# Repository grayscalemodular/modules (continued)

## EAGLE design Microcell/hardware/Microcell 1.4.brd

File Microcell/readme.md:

Microcell
=======

[microcell](https://microcell.cc) is a Eurorack synthesizer module created by [Grayscale](https://grayscale.info/). It is primarily based on [Clouds](https://mutable-instruments.net/modules/clouds/) by [Mutable Instruments](https://mutable-instruments.net/), which was discontinued in 2017. The original source files for Clouds can be found in the Mutable Instruments [Github](https://github.com/pichenettes/eurorack) repository.

Visit [microcell.cc](https://microcell.cc) for more information.

Hardware
=======

The schematic and PCB files for this project are distributed under the Creative Commons [CC-BY-SA 3.0](https://creativecommons.org/licenses/by-sa/3.0/) license, the same license used by the Clouds source files.

CC BY-SA license terms do not confer the right to use intellectual property such as trademarks, brand names, and logos. Grayscale, Microcell, Mutable Instruments, and Clouds are trademarks of their respective owners and should not be used without permission.

Firmware
=======

Microcell ships with the Superparasites firmware, which combines elements of the original Clouds DSP code by [Mutable Instruments](https://github.com/pichenettes/eurorack), the [Parasites](https://mqtthiqs.github.io/parasites/clouds.html) alternate firmware by Matthias Puech, and the [Beat Repeat](https://github.com/jkammerl/eurorack) alternate firmware by Julius Kammerl. All source code is available on the [GitHub repo](https://github.com/patrickdowling/superparasites) maintained by Patrick Dowling. Thanks to all involved for their work on this hybrid code base.

Source code for this project is distributed under the MIT License. See [github.com/patrickdowling/superparasites](https://github.com/patrickdowling/superparasites) for source code.

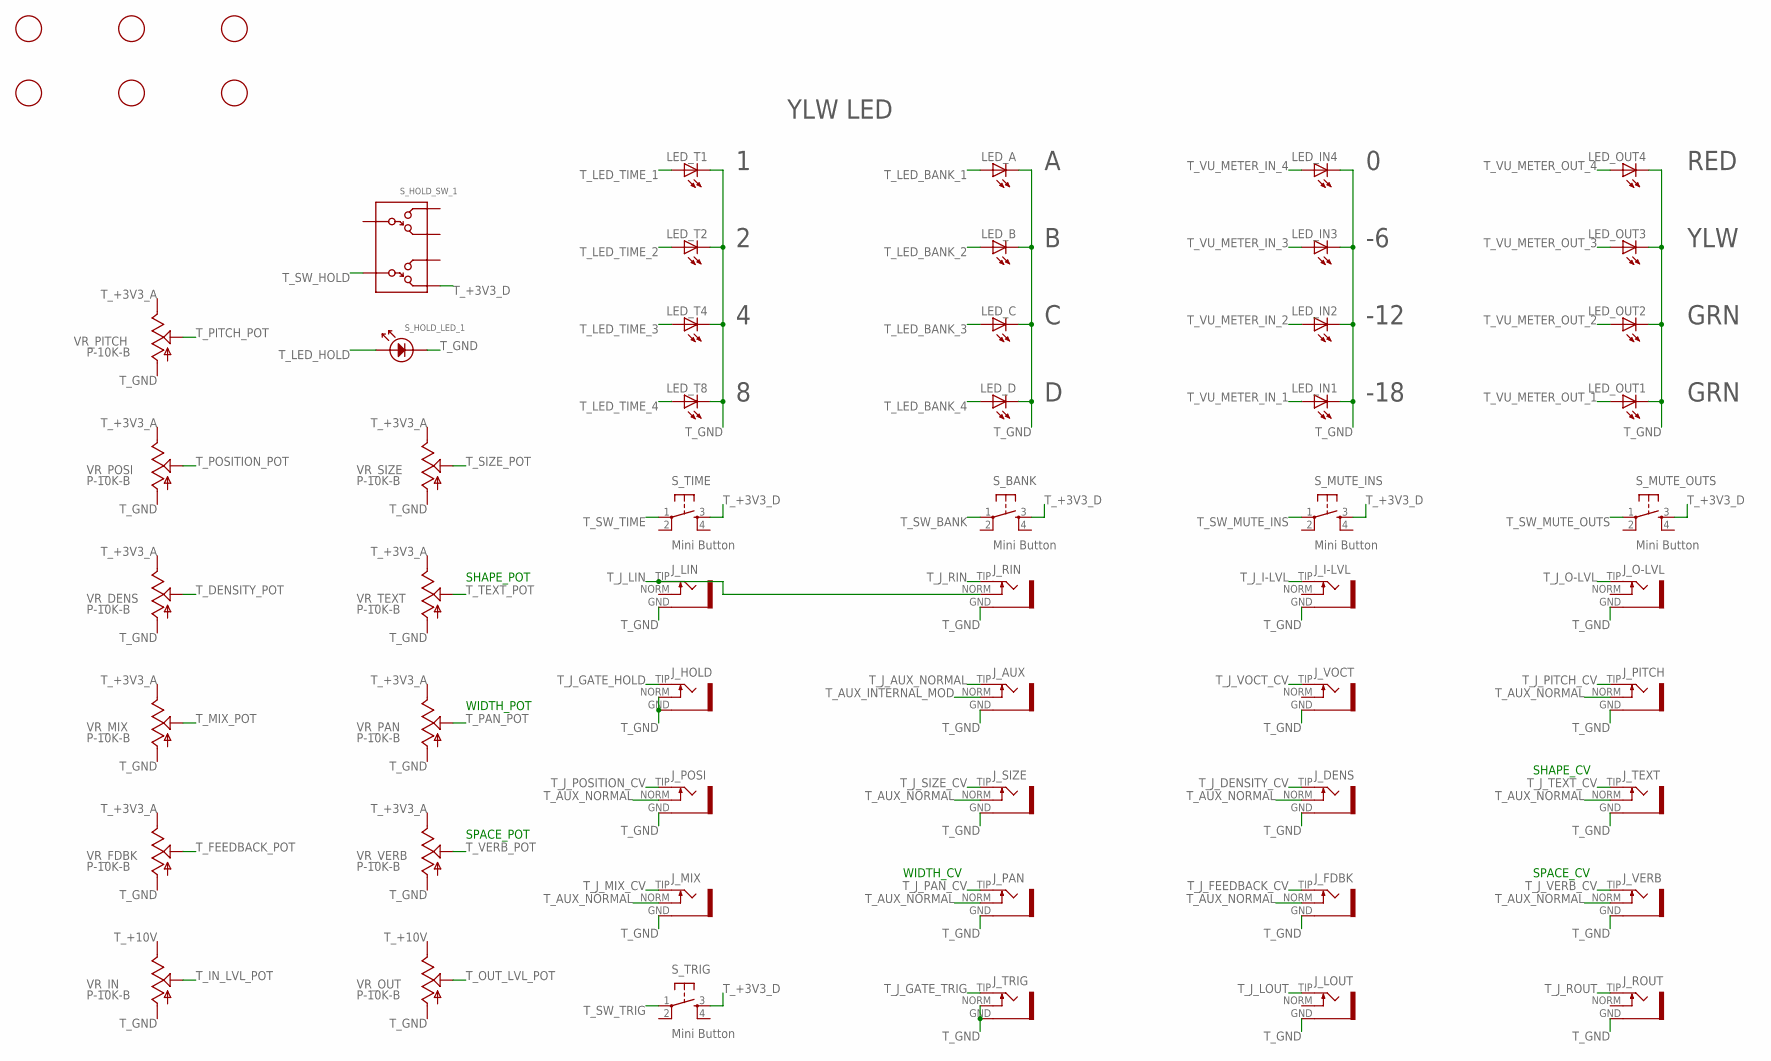
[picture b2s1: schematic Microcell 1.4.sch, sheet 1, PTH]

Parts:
FD1, FD2, FD3, FD4, FD5, FD6: FIDUCIAL; FIDUCIAL_1MM
J_AUX: Eurorack Jack; S_JACK_SMALL_SILK
J_DENS: Eurorack Jack; S_JACK_SILK
J_FDBK: Eurorack Jack; S_JACK_SILK
J_HOLD: Eurorack Jack; S_JACK_SMALL_SILK
J_I-LVL: Eurorack Jack; S_JACK_SILK
J_LIN: Eurorack Jack; S_JACK_SILK
J_LOUT: Eurorack Jack; S_JACK_SILK
J_MIX: Eurorack Jack; S_JACK_SILK
J_O-LVL: Eurorack Jack; S_JACK_SILK
J_PAN: Eurorack Jack; S_JACK_SILK
J_PITCH: Eurorack Jack; S_JACK_SILK
J_POSI: Eurorack Jack; S_JACK_SILK
J_RIN: Eurorack Jack; S_JACK_SILK
J_ROUT: Eurorack Jack; S_JACK_SILK
J_SIZE: Eurorack Jack; S_JACK_SILK
J_TEXT: Eurorack Jack; S_JACK_SILK
J_TRIG: Eurorack Jack; S_JACK_SMALL_SILK
J_VERB: Eurorack Jack; S_JACK_SILK
J_VOCT: Eurorack Jack; S_JACK_SILK
LED_A: 3mm Yellow Diffused; LED_SILK
LED_B: 3mm Yellow Diffused; LED_SILK
LED_C: 3mm Yellow Diffused; LED_SILK
LED_D: 3mm Yellow Diffused; LED_SILK
LED_IN1, LED_IN2: 3mm Green Diffused; LED_SILK
LED_IN3: 3mm Yellow Diffused; LED_SILK
LED_IN4: 3mm Red Diffused; LED_SILK
LED_OUT1, LED_OUT2: 3mm Green Diffused; LED_SILK
LED_OUT3: 3mm Yellow Diffused; LED_SILK
LED_OUT4: 3mm Red Diffused; LED_SILK
LED_T1, LED_T2, LED_T4, LED_T8: 3mm Yellow Diffused; LED_SILK
S_BANK: Mini Button; TACTILE-PTH_SILK
S_HOLD: LED Button White; LED_BUTTON_SILK
S_MUTE_INS: Mini Button; TACTILE-PTH_SILK
S_MUTE_OUTS: Mini Button; TACTILE-PTH_SILK
S_TIME: Mini Button; TACTILE-PTH_SILK
S_TRIG: Mini Button; TACTILE-PTH_SILK
VR_DENS: P-10K-B; 9MM_SNAP-IN_POT_SILK
VR_FDBK: P-10K-B; 9MM_SNAP-IN_POT_SILK
VR_IN: P-10K-B; 9MM_SNAP-IN_POT_SILK
VR_MIX: P-10K-B; 9MM_SNAP-IN_POT_SILK
VR_OUT: P-10K-B; 9MM_SNAP-IN_POT_SILK
VR_PAN: P-10K-B; 9MM_SNAP-IN_POT_SILK
VR_PITCH: P-10K-B; 9MM_SNAP-IN_POT_SILK
VR_POSI: P-10K-B; 9MM_SNAP-IN_POT_SILK
VR_SIZE: P-10K-B; 9MM_SNAP-IN_POT_SILK
VR_TEXT: P-10K-B; 9MM_SNAP-IN_POT_SILK
VR_VERB: P-10K-B; 9MM_SNAP-IN_POT_SILK

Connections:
T_+3V3_A: VR_DENS.3, VR_FDBK.3, VR_MIX.3, VR_PAN.3, VR_PITCH.3, VR_POSI.3, VR_SIZE.3, VR_TEXT.3, VR_VERB.3; also elsewhere on the board
T_+3V3_D: S_BANK.3, S_HOLD.3, S_MUTE_INS.3, S_MUTE_OUTS.3, S_TIME.3, S_TRIG.3; also elsewhere on the board
T_+10V: VR_IN.3, VR_OUT.3; also elsewhere on the board
T_AUX_INTERNAL_MOD: J_AUX.NORM; also elsewhere on the board
T_AUX_NORMAL: J_DENS.NORM, J_FDBK.NORM, J_MIX.NORM, J_PAN.NORM, J_PITCH.NORM, J_POSI.NORM, J_SIZE.NORM, J_TEXT.NORM, J_VERB.NORM; also elsewhere on the board
T_DENSITY_POT: VR_DENS.2; also elsewhere on the board
T_FEEDBACK_POT: VR_FDBK.2; also elsewhere on the board
T_GND: J_AUX.GND, J_DENS.GND, J_FDBK.GND, J_HOLD.GND, J_HOLD.NORM, J_I-LVL.GND, J_LIN.GND, J_LOUT.GND, J_MIX.GND, J_O-LVL.GND, J_PAN.GND, J_PITCH.GND, J_POSI.GND, J_RIN.GND, J_ROUT.GND, J_SIZE.GND, J_TEXT.GND, J_TRIG.GND, J_TRIG.NORM, J_VERB.GND, J_VOCT.GND, LED_A.K (C), LED_B.K (C), LED_C.K (C), LED_D.K (C), LED_IN1.K (C), LED_IN2.K (C), LED_IN3.K (C), LED_IN4.K (C), LED_OUT1.K (C), LED_OUT2.K (C), LED_OUT3.K (C), LED_OUT4.K (C), LED_T1.K (C), LED_T2.K (C), LED_T4.K (C), LED_T8.K (C), S_HOLD.LED_K, VR_DENS.1, VR_FDBK.1, VR_IN.1, VR_MIX.1, VR_OUT.1, VR_PAN.1, VR_PITCH.1, VR_POSI.1, VR_SIZE.1, VR_TEXT.1, VR_VERB.1; also elsewhere on the board
T_IN_LVL_POT: VR_IN.2; also elsewhere on the board
T_J_AUX_NORMAL: J_AUX.TIP; also elsewhere on the board
T_J_DENSITY_CV: J_DENS.TIP; also elsewhere on the board
T_J_FEEDBACK_CV: J_FDBK.TIP; also elsewhere on the board
T_J_GATE_HOLD: J_HOLD.TIP; also elsewhere on the board
T_J_GATE_TRIG: J_TRIG.TIP; also elsewhere on the board
T_J_I-LVL: J_I-LVL.TIP; also elsewhere on the board
T_J_LIN: J_LIN.TIP, J_RIN.NORM; also elsewhere on the board
T_J_LOUT: J_LOUT.TIP; also elsewhere on the board
T_J_MIX_CV: J_MIX.TIP; also elsewhere on the board
T_J_O-LVL: J_O-LVL.TIP; also elsewhere on the board
T_J_PAN_CV: J_PAN.TIP; also elsewhere on the board
T_J_PITCH_CV: J_PITCH.TIP; also elsewhere on the board
T_J_POSITION_CV: J_POSI.TIP; also elsewhere on the board
T_J_RIN: J_RIN.TIP; also elsewhere on the board
T_J_ROUT: J_ROUT.TIP; also elsewhere on the board
T_J_SIZE_CV: J_SIZE.TIP; also elsewhere on the board
T_J_TEXT_CV: J_TEXT.TIP; also elsewhere on the board
T_J_VERB_CV: J_VERB.TIP; also elsewhere on the board
T_J_VOCT_CV: J_VOCT.TIP; also elsewhere on the board
T_LED_BANK_1: LED_A.A; also elsewhere on the board
T_LED_BANK_2: LED_B.A; also elsewhere on the board
T_LED_BANK_3: LED_C.A; also elsewhere on the board
T_LED_BANK_4: LED_D.A; also elsewhere on the board
T_LED_HOLD: S_HOLD.LED_A; also elsewhere on the board
T_LED_TIME_1: LED_T1.A; also elsewhere on the board
T_LED_TIME_2: LED_T2.A; also elsewhere on the board
T_LED_TIME_3: LED_T4.A; also elsewhere on the board
T_LED_TIME_4: LED_T8.A; also elsewhere on the board
T_MIX_POT: VR_MIX.2; also elsewhere on the board
T_OUT_LVL_POT: VR_OUT.2; also elsewhere on the board
T_PAN_POT: VR_PAN.2; also elsewhere on the board
T_PITCH_POT: VR_PITCH.2; also elsewhere on the board
T_POSITION_POT: VR_POSI.2; also elsewhere on the board
T_SIZE_POT: VR_SIZE.2; also elsewhere on the board
T_SW_BANK: S_BANK.1; also elsewhere on the board
T_SW_HOLD: S_HOLD.2; also elsewhere on the board
T_SW_MUTE_INS: S_MUTE_INS.1; also elsewhere on the board
T_SW_MUTE_OUTS: S_MUTE_OUTS.1; also elsewhere on the board
T_SW_TIME: S_TIME.1; also elsewhere on the board
T_SW_TRIG: S_TRIG.1; also elsewhere on the board
T_TEXT_POT: VR_TEXT.2; also elsewhere on the board
T_VERB_POT: VR_VERB.2; also elsewhere on the board
T_VU_METER_IN_1: LED_IN1.A; also elsewhere on the board
T_VU_METER_IN_2: LED_IN2.A; also elsewhere on the board
T_VU_METER_IN_3: LED_IN3.A; also elsewhere on the board
T_VU_METER_IN_4: LED_IN4.A; also elsewhere on the board
T_VU_METER_OUT_1: LED_OUT1.A; also elsewhere on the board
T_VU_METER_OUT_2: LED_OUT2.A; also elsewhere on the board
T_VU_METER_OUT_3: LED_OUT3.A; also elsewhere on the board
T_VU_METER_OUT_4: LED_OUT4.A; also elsewhere on the board

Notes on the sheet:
-12
-18
GRN
YLW
RED
YLW LED
SPACE_CV
SHAPE_CV
WIDTH_CV
WIDTH_POT
SHAPE_POT
SPACE_POT

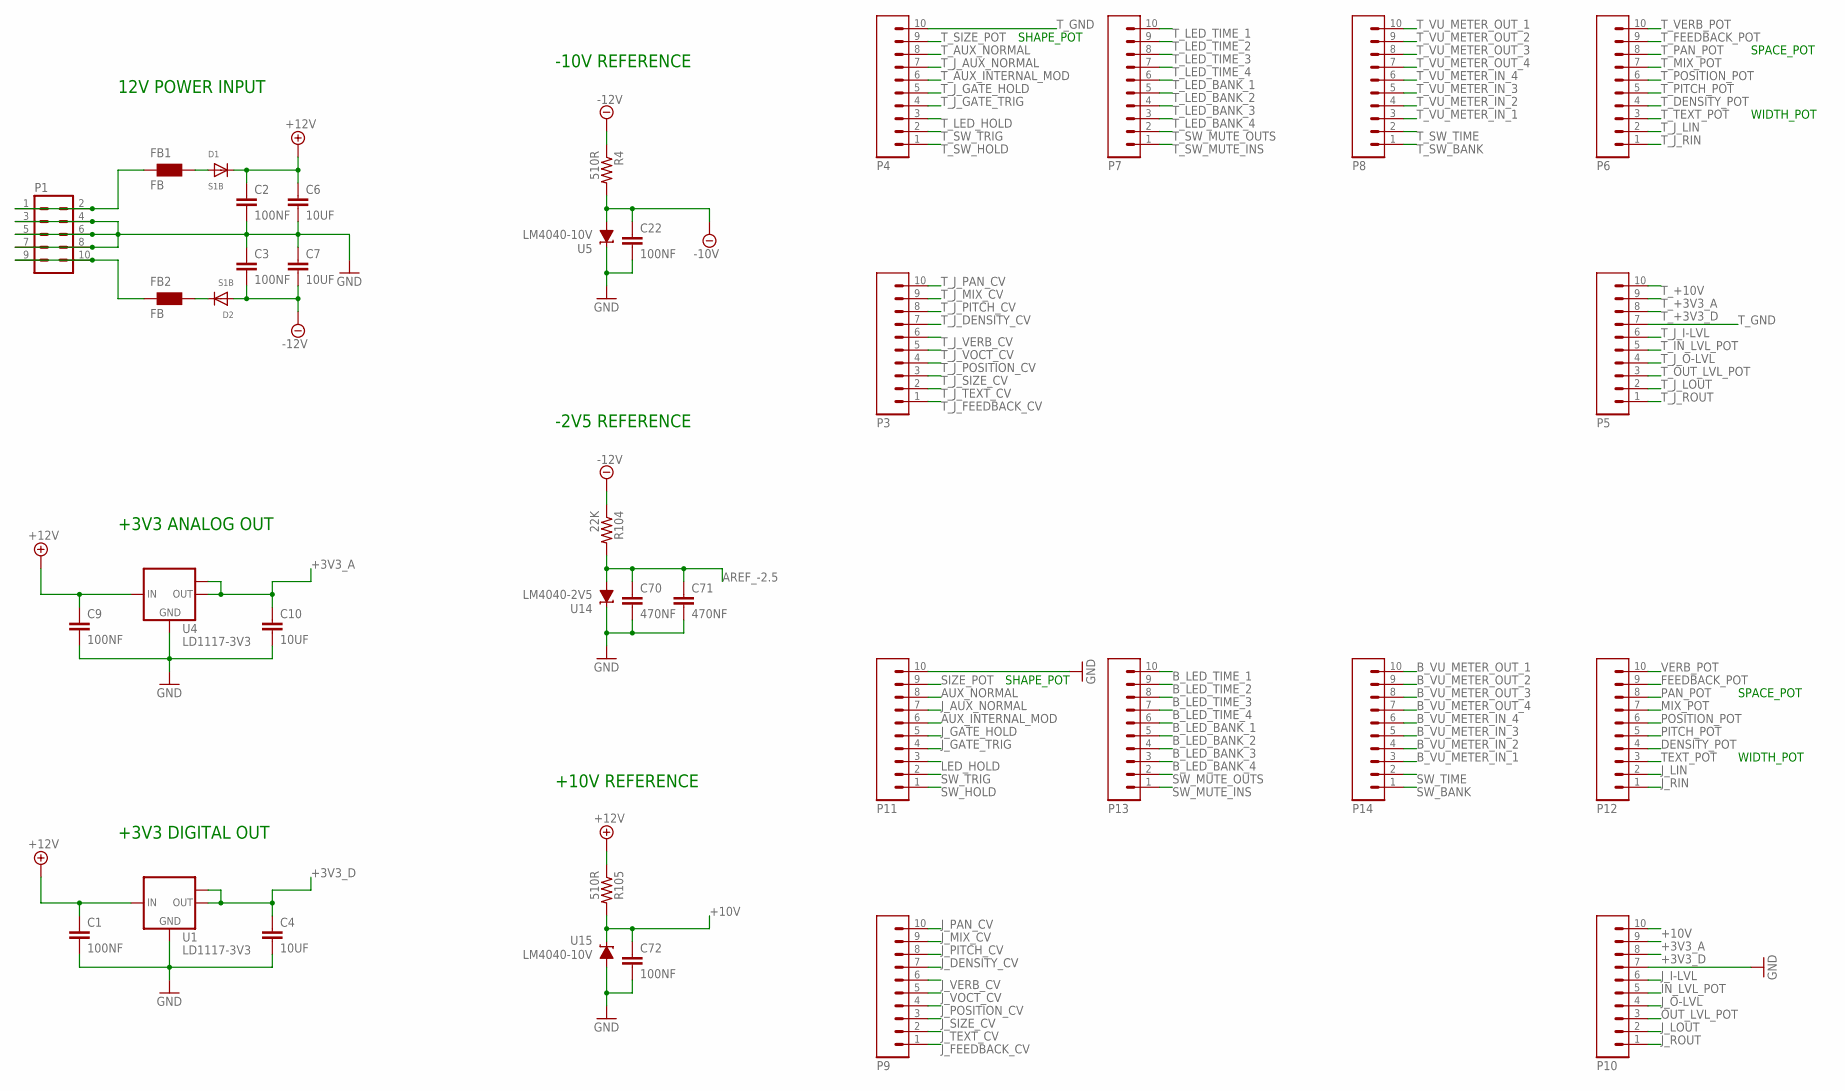
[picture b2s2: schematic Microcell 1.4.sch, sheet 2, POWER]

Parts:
C1, C2, C3, C9, C22, C72: 100NF; C0603
C4, C6, C7, C10: 10UF; C0805
C70, C71: 470NF; C0603
D1, D2: S1B; SMADIODE
FB1, FB2: FB; WUERTH-ELEKTRONIK_0603
P1: 2X5 Male PTH Header; 2X5_LOCK
P3, P4, P5, P6, P7, P8: 1X10 Female PTH header; 1X10_NO_SILK
P9, P10, P11, P12, P13, P14: 1X10 Male PTH header; 1X10_NO_SILK
R4, R105: 510R; R0603
R104: 22K; R0603
U1, U4: LD1117-3V3; SOT223
U5, U15: LM4040-10V; DBZ_R-PDSO-G3
U14: LM4040-2V5; DBZ_R-PDSO-G3

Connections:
+3V3_A: C10.1, P10.9, U4.2 (OUT), U4.TAB (OUT1); also elsewhere on the board
+3V3_D: C4.1, P10.8, U1.2 (OUT), U1.TAB (OUT1); also elsewhere on the board
+10V: C72.1, P10.10, R105.2, U15.1 (C)
+12V: C1.1, C2.1, C6.1, C9.1, D1.C, R105.1, U1.3 (IN), U4.3 (IN); also elsewhere on the board
-10V: C22.1, R4.2, U5.2 (A); also elsewhere on the board
-12V: C3.2, C7.2, D2.A, R4.1, R104.1; also elsewhere on the board
AREF_-2.5: C70.1, C71.1, R104.2, U14.2 (A); also elsewhere on the board
AUX_INTERNAL_MOD: P11.6; also elsewhere on the board
AUX_NORMAL: P11.8; also elsewhere on the board
B_LED_BANK_1: P13.6; also elsewhere on the board
B_LED_BANK_2: P13.5; also elsewhere on the board
B_LED_BANK_3: P13.4; also elsewhere on the board
B_LED_BANK_4: P13.3; also elsewhere on the board
B_LED_TIME_1: P13.10; also elsewhere on the board
B_LED_TIME_2: P13.9; also elsewhere on the board
B_LED_TIME_3: P13.8; also elsewhere on the board
B_LED_TIME_4: P13.7; also elsewhere on the board
B_VU_METER_IN_1: P14.3; also elsewhere on the board
B_VU_METER_IN_2: P14.4; also elsewhere on the board
B_VU_METER_IN_3: P14.5; also elsewhere on the board
B_VU_METER_IN_4: P14.6; also elsewhere on the board
B_VU_METER_OUT_1: P14.10; also elsewhere on the board
B_VU_METER_OUT_2: P14.9; also elsewhere on the board
B_VU_METER_OUT_3: P14.8; also elsewhere on the board
B_VU_METER_OUT_4: P14.7; also elsewhere on the board
DENSITY_POT: P12.4; also elsewhere on the board
FEEDBACK_POT: P12.9; also elsewhere on the board
GND: C1.2, C2.2, C3.1, C4.2, C6.2, C7.1, C9.2, C10.2, C22.2, C70.2, C71.2, C72.2, P1.3, P1.4, P1.5, P1.6, P1.7, P1.8, P10.7, P11.10, U1.1 (GND), U4.1 (GND), U5.1 (C), U14.1 (C), U15.2 (A); also elsewhere on the board
IN_LVL_POT: P10.5; also elsewhere on the board
J_AUX_NORMAL: P11.7; also elsewhere on the board
J_DENSITY_CV: P9.7; also elsewhere on the board
J_FEEDBACK_CV: P9.1; also elsewhere on the board
J_GATE_HOLD: P11.5; also elsewhere on the board
J_GATE_TRIG: P11.4; also elsewhere on the board
J_I-LVL: P10.6; also elsewhere on the board
J_LIN: P12.2; also elsewhere on the board
J_LOUT: P10.2; also elsewhere on the board
J_MIX_CV: P9.9; also elsewhere on the board
J_O-LVL: P10.4; also elsewhere on the board
J_PAN_CV: P9.10; also elsewhere on the board
J_PITCH_CV: P9.8; also elsewhere on the board
J_POSITION_CV: P9.4; also elsewhere on the board
J_RIN: P12.1; also elsewhere on the board
J_ROUT: P10.1; also elsewhere on the board
J_SIZE_CV: P9.3; also elsewhere on the board
J_TEXT_CV: P9.2; also elsewhere on the board
J_VERB_CV: P9.6; also elsewhere on the board
J_VOCT_CV: P9.5; also elsewhere on the board
LED_HOLD: P11.3; also elsewhere on the board
MIX_POT: P12.7; also elsewhere on the board
unnamed: D1.A, FB1.2
unnamed: FB1.1, P1.1, P1.2
unnamed: D2.C, FB2.2
unnamed: FB2.1, P1.9, P1.10
OUT_LVL_POT: P10.3; also elsewhere on the board
PAN_POT: P12.8; also elsewhere on the board
PITCH_POT: P12.5; also elsewhere on the board
POSITION_POT: P12.6; also elsewhere on the board
SIZE_POT: P11.9; also elsewhere on the board
SW_BANK: P14.1; also elsewhere on the board
SW_HOLD: P11.1; also elsewhere on the board
SW_MUTE_INS: P13.1; also elsewhere on the board
SW_MUTE_OUTS: P13.2; also elsewhere on the board
SW_TIME: P14.2; also elsewhere on the board
SW_TRIG: P11.2; also elsewhere on the board
TEXT_POT: P12.3; also elsewhere on the board
T_+3V3_A: P5.9; also elsewhere on the board
T_+3V3_D: P5.8; also elsewhere on the board
T_+10V: P5.10; also elsewhere on the board
T_AUX_INTERNAL_MOD: P4.6; also elsewhere on the board
T_AUX_NORMAL: P4.8; also elsewhere on the board
T_DENSITY_POT: P6.4; also elsewhere on the board
T_FEEDBACK_POT: P6.9; also elsewhere on the board
T_GND: P4.10, P5.7; also elsewhere on the board
T_IN_LVL_POT: P5.5; also elsewhere on the board
T_J_AUX_NORMAL: P4.7; also elsewhere on the board
T_J_DENSITY_CV: P3.7; also elsewhere on the board
T_J_FEEDBACK_CV: P3.1; also elsewhere on the board
T_J_GATE_HOLD: P4.5; also elsewhere on the board
T_J_GATE_TRIG: P4.4; also elsewhere on the board
T_J_I-LVL: P5.6; also elsewhere on the board
T_J_LIN: P6.2; also elsewhere on the board
T_J_LOUT: P5.2; also elsewhere on the board
T_J_MIX_CV: P3.9; also elsewhere on the board
T_J_O-LVL: P5.4; also elsewhere on the board
T_J_PAN_CV: P3.10; also elsewhere on the board
T_J_PITCH_CV: P3.8; also elsewhere on the board
T_J_POSITION_CV: P3.4; also elsewhere on the board
T_J_RIN: P6.1; also elsewhere on the board
T_J_ROUT: P5.1; also elsewhere on the board
T_J_SIZE_CV: P3.3; also elsewhere on the board
T_J_TEXT_CV: P3.2; also elsewhere on the board
T_J_VERB_CV: P3.6; also elsewhere on the board
T_J_VOCT_CV: P3.5; also elsewhere on the board
T_LED_BANK_1: P7.6; also elsewhere on the board
T_LED_BANK_2: P7.5; also elsewhere on the board
T_LED_BANK_3: P7.4; also elsewhere on the board
T_LED_BANK_4: P7.3; also elsewhere on the board
T_LED_HOLD: P4.3; also elsewhere on the board
T_LED_TIME_1: P7.10; also elsewhere on the board
T_LED_TIME_2: P7.9; also elsewhere on the board
T_LED_TIME_3: P7.8; also elsewhere on the board
T_LED_TIME_4: P7.7; also elsewhere on the board
T_MIX_POT: P6.7; also elsewhere on the board
T_OUT_LVL_POT: P5.3; also elsewhere on the board
T_PAN_POT: P6.8; also elsewhere on the board
T_PITCH_POT: P6.5; also elsewhere on the board
T_POSITION_POT: P6.6; also elsewhere on the board
T_SIZE_POT: P4.9; also elsewhere on the board
T_SW_BANK: P8.1; also elsewhere on the board
T_SW_HOLD: P4.1; also elsewhere on the board
T_SW_MUTE_INS: P7.1; also elsewhere on the board
T_SW_MUTE_OUTS: P7.2; also elsewhere on the board
T_SW_TIME: P8.2; also elsewhere on the board
T_SW_TRIG: P4.2; also elsewhere on the board
T_TEXT_POT: P6.3; also elsewhere on the board
T_VERB_POT: P6.10; also elsewhere on the board
T_VU_METER_IN_1: P8.3; also elsewhere on the board
T_VU_METER_IN_2: P8.4; also elsewhere on the board
T_VU_METER_IN_3: P8.5; also elsewhere on the board
T_VU_METER_IN_4: P8.6; also elsewhere on the board
T_VU_METER_OUT_1: P8.10; also elsewhere on the board
T_VU_METER_OUT_2: P8.9; also elsewhere on the board
T_VU_METER_OUT_3: P8.8; also elsewhere on the board
T_VU_METER_OUT_4: P8.7; also elsewhere on the board
VERB_POT: P12.10; also elsewhere on the board

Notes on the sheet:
12V POWER INPUT
+3V3 ANALOG OUT
+3V3 DIGITAL OUT
-10V REFERENCE
-2V5 REFERENCE
+10V REFERENCE
SHAPE_POT
WIDTH_POT
SPACE_POT

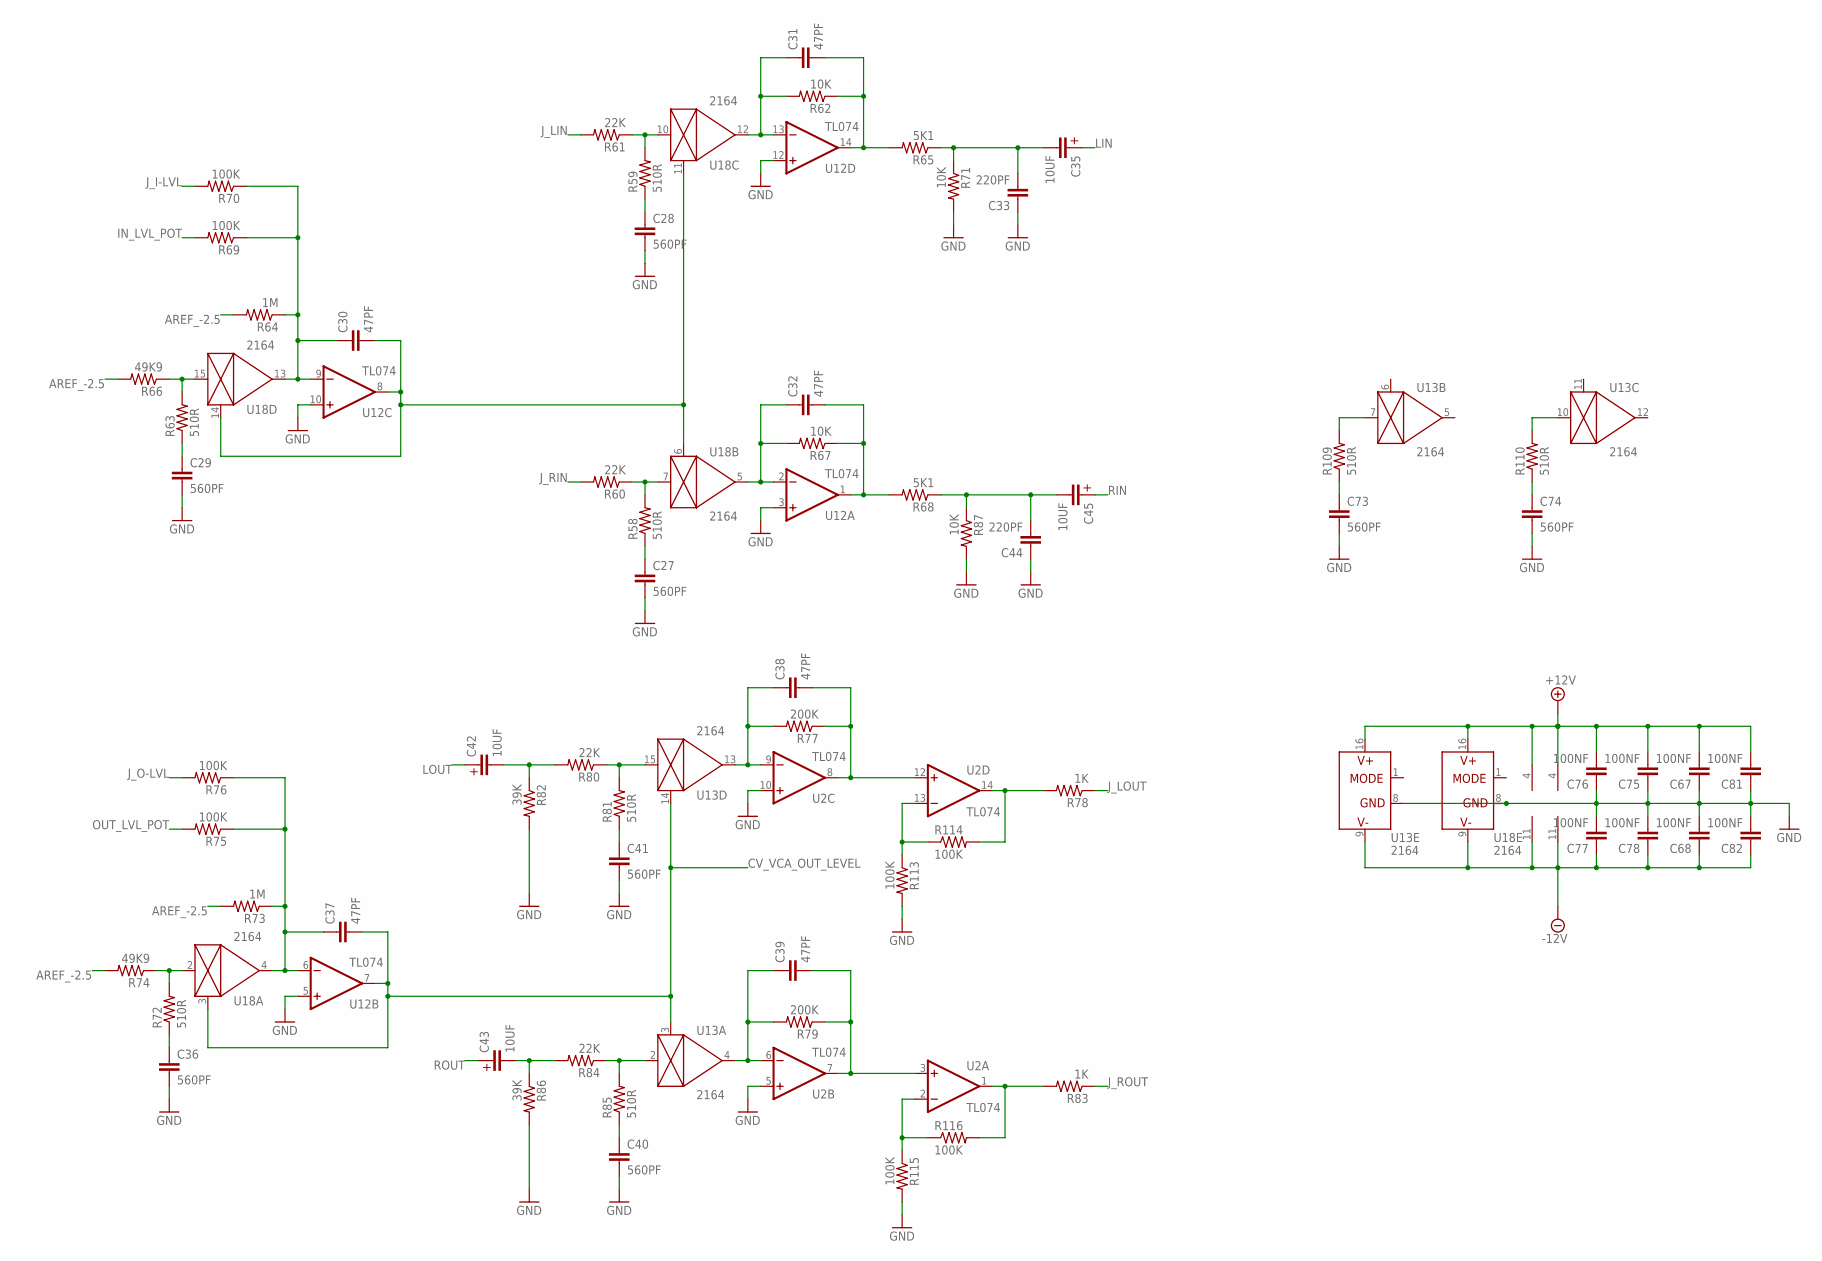
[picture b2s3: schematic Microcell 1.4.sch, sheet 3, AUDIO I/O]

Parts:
C27, C28, C29, C36, C40, C41, C73, C74: 560PF; C0603
C30, C31, C32, C37, C38, C39: 47PF; C0603
C33, C44: 220PF; C0603
C35, C42, C43, C45: 10UF; EC-4X7
C67, C68, C75, C76, C77, C78, C81, C82: 100NF; C0603
R58, R59, R63, R72, R81, R85, R109, R110: 510R; R0603
R60, R61, R80, R84: 22K; R0603
R62, R67, R71, R87: 10K; R0603
R64, R73: 1M; R0603
R65, R68: 5K1; R0603
R66, R74: 49K9; R0603
R69, R70, R75, R76, R113, R114, R115, R116: 100K; R0603
R77, R79: 200K; R0603
R78, R83: 1K; R0603
R82, R86: 39K; R0603
U2, U12: TL074; SO-14
U13, U18: 2164; SO-16

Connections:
+12V: C67.2, C75.2, C76.2, C81.2, U2.4 (V+), U12.4 (V+), U13.16 (V+), U18.16 (V+); also elsewhere on the board
-12V: C68.1, C77.1, C78.1, C82.1, U2.11 (V-), U12.11 (V-), U13.9 (V-), U18.9 (V-); also elsewhere on the board
AREF_-2.5: R64.2, R66.2, R73.2, R74.2; also elsewhere on the board
CV_VCA_OUT_LEVEL: C37.2, U12.7 (OUT), U13.3 (CTRL), U13.14 (CTRL), U18.3 (CTRL); also elsewhere on the board
GND: C27.2, C28.2, C29.2, C33.1, C36.2, C40.2, C41.2, C44.1, C67.1, C68.2, C73.2, C74.2, C75.1, C76.1, C77.2, C78.2, C81.1, C82.2, R71.2, R82.2, R86.2, R87.2, R113.2, R115.2, U2.5 (+IN), U2.10 (+IN), U12.3 (+IN), U12.5 (+IN), U12.10 (+IN), U12.12 (+IN), U13.8 (GND), U18.8 (GND); also elsewhere on the board
IN_LVL_POT: R69.2; also elsewhere on the board
J_I-LVL: R70.2; also elsewhere on the board
J_LIN: R61.2; also elsewhere on the board
J_LOUT: R78.1; also elsewhere on the board
J_O-LVL: R76.2; also elsewhere on the board
J_RIN: R60.2; also elsewhere on the board
J_ROUT: R83.1; also elsewhere on the board
LIN: C35.P$1 (POS); also elsewhere on the board
LOUT: C42.P$1 (POS); also elsewhere on the board
unnamed: C28.1, R59.1
unnamed: C27.1, R58.1
unnamed: C29.1, R63.1
unnamed: C30.2, U12.8 (OUT), U18.6 (CTRL), U18.11 (CTRL), U18.14 (CTRL)
unnamed: R58.2, R60.1, U18.7 (IN)
unnamed: R63.2, R66.1, U18.15 (IN)
unnamed: C32.1, R67.2, U12.2 (-IN), U18.5 (OUT)
unnamed: C32.2, R67.1, R68.2, U12.1 (OUT)
unnamed: C36.1, R72.1
unnamed: R72.2, R74.1, U18.2 (IN)
unnamed: C38.1, R77.2, U2.9 (-IN), U13.13 (OUT)
unnamed: C38.2, R77.1, U2.8 (OUT), U2.12 (+IN)
unnamed: R59.2, R61.1, U18.10 (IN)
unnamed: R109.2, U13.7 (IN)
unnamed: R80.1, R81.2, U13.15 (IN)
unnamed: C41.1, R81.1
unnamed: C42.P$2 (NEG), R80.2, R82.1
unnamed: C44.2, C45.P$2 (NEG), R68.1, R87.1
unnamed: C39.1, R79.2, U2.6 (-IN), U13.4 (OUT)
unnamed: C39.2, R79.1, U2.3 (+IN), U2.7 (OUT)
unnamed: R84.1, R85.2, U13.2 (IN)
unnamed: C40.1, R85.1
unnamed: C43.P$2 (NEG), R84.2, R86.1
unnamed: R110.2, U13.10 (IN)
unnamed: C31.1, R62.2, U12.13 (-IN), U18.12 (OUT)
unnamed: C31.2, R62.1, R65.2, U12.14 (OUT)
unnamed: R113.1, R114.1, U2.13 (-IN)
unnamed: C73.1, R109.1
unnamed: C74.1, R110.1
unnamed: R78.2, R114.2, U2.14 (OUT)
unnamed: R115.1, R116.1, U2.2 (-IN)
unnamed: R83.2, R116.2, U2.1 (OUT)
unnamed: C33.2, C35.P$2 (NEG), R65.1, R71.1
OUT_LVL_POT: R75.2; also elsewhere on the board
RIN: C45.P$1 (POS); also elsewhere on the board
ROUT: C43.P$1 (POS); also elsewhere on the board
VCA_CTRL_INPUTS: C30.1, R64.1, R69.1, R70.1, U12.9 (-IN), U18.13 (OUT)
VCA_CTRL_INPUTS1: C37.1, R73.1, R75.1, R76.1, U12.6 (-IN), U18.4 (OUT)

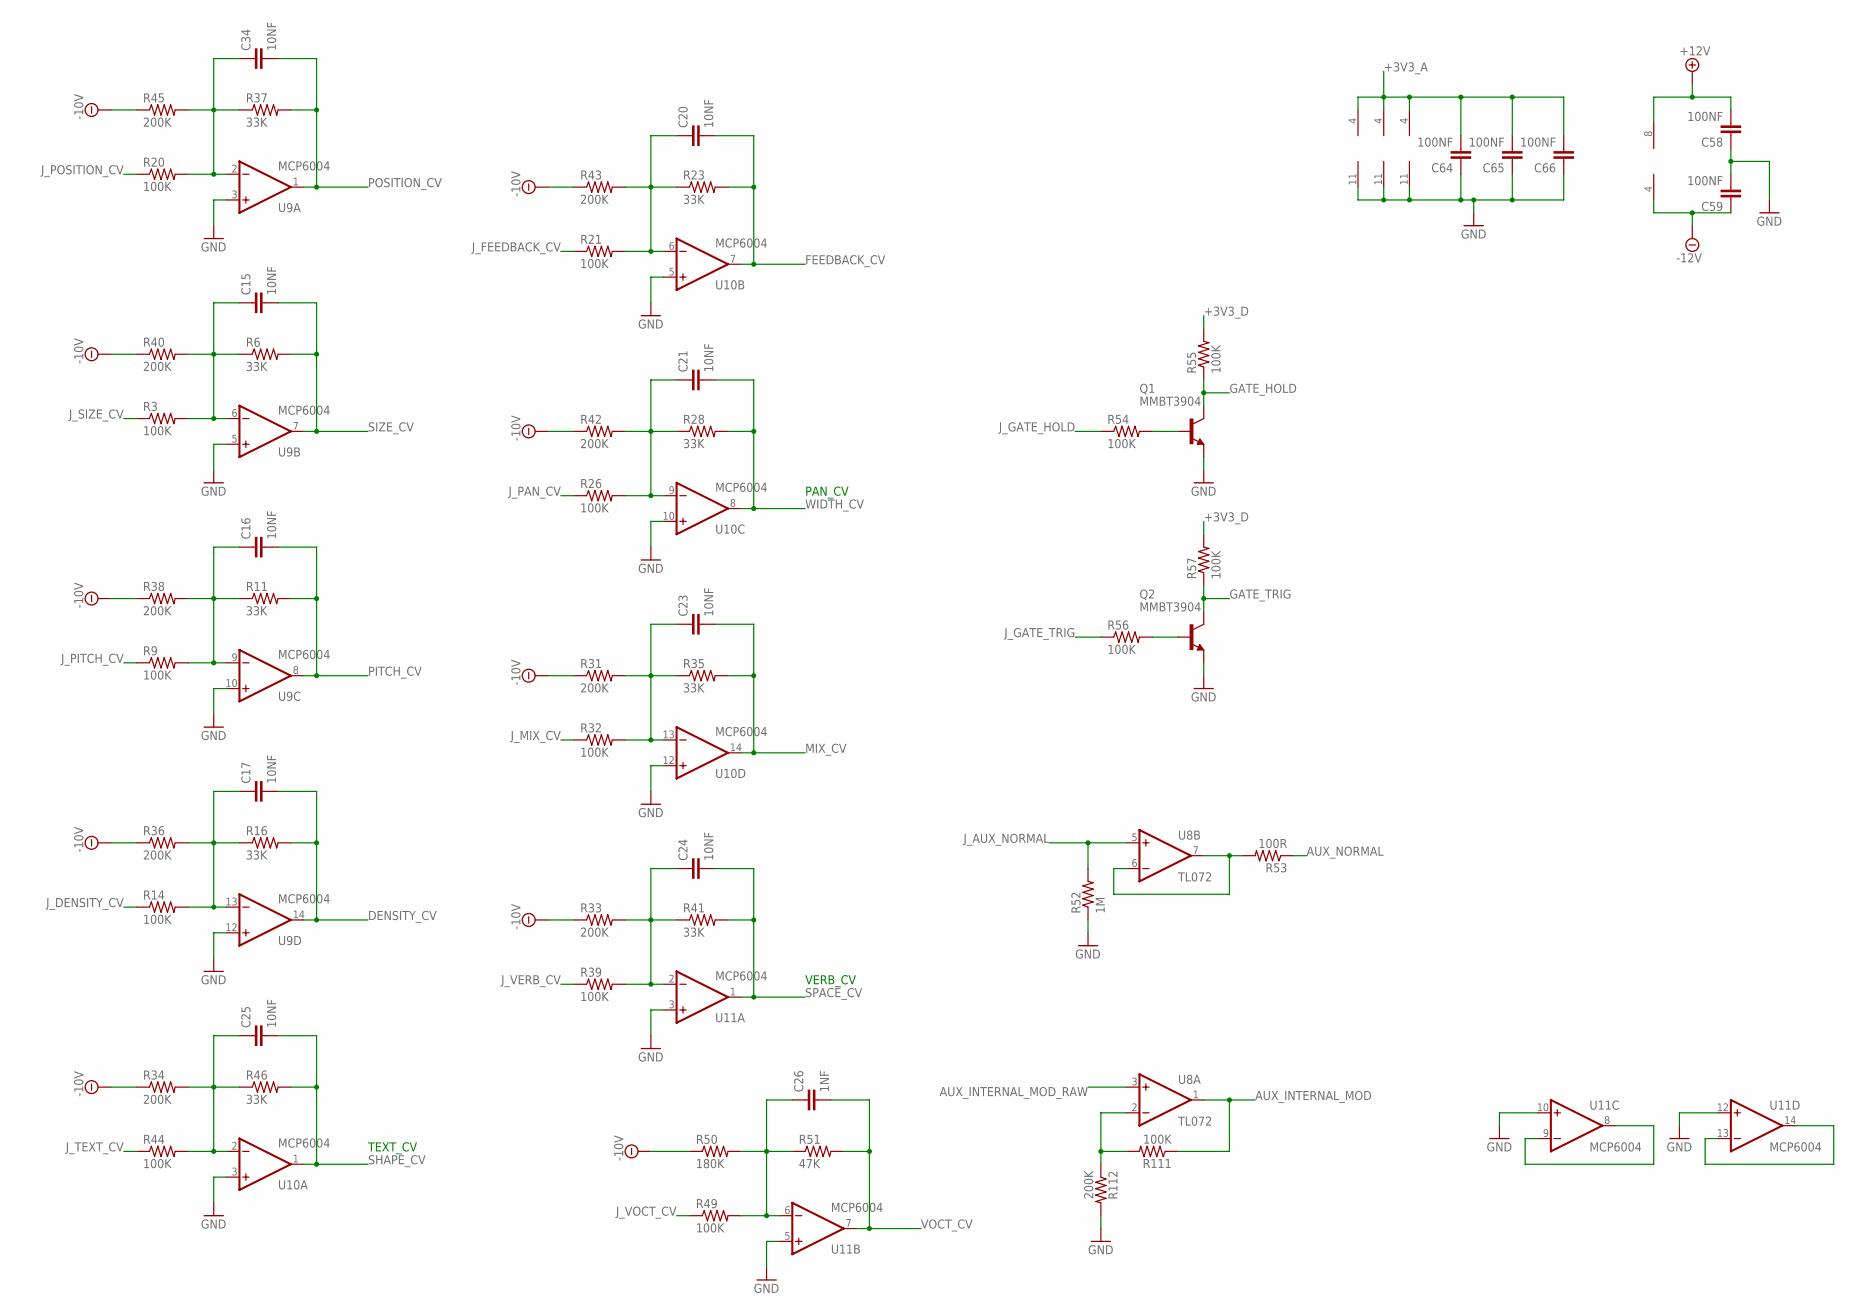
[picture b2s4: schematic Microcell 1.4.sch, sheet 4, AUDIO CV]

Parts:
C15, C16, C17, C20, C21, C23, C24, C25, C34: 10NF; C0603
C26: 1NF; C0603
C58, C59, C64, C65, C66: 100NF; C0603
Q1, Q2: MMBT3904; SOT23-BEC
R3, R9, R14, R20, R21, R26, R32, R39, R44, R49, R54, R55, R56, R57, R111: 100K; R0603
R6, R11, R16, R23, R28, R35, R37, R41, R46: 33K; R0603
R31, R33, R34, R36, R38, R40, R42, R43, R45, R112: 200K; R0603
R50: 180K; R0603
R51: 47K; R0603
R52: 1M; R0603
R53: 100R; R0603
U8: TL072; SO-8
U9, U10, U11: MCP6004; SO-14

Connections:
+3V3_A: C64.2, C65.2, C66.2, U9.4 (V+), U10.4 (V+), U11.4 (V+); also elsewhere on the board
+3V3_D: R55.2, R57.2; also elsewhere on the board
+12V: C58.2, U8.8 (V+); also elsewhere on the board
-10V: R31.1, R33.1, R34.1, R36.1, R38.1, R40.1, R42.1, R43.1, R45.1, R50.1; also elsewhere on the board
-12V: C59.1, U8.4 (V-); also elsewhere on the board
AUX_INTERNAL_MOD: R111.1, U8.1 (OUT); also elsewhere on the board
AUX_INTERNAL_MOD_RAW: U8.3 (+IN); also elsewhere on the board
AUX_NORMAL: R53.1; also elsewhere on the board
DENSITY_CV: C17.2, R16.2, U9.14 (OUT); also elsewhere on the board
FEEDBACK_CV: C20.2, R23.2, U10.7 (OUT); also elsewhere on the board
GATE_HOLD: Q1.C, R55.1; also elsewhere on the board
GATE_TRIG: Q2.C, R57.1; also elsewhere on the board
GND: C58.1, C59.2, C64.1, C65.1, C66.1, Q1.E, Q2.E, R52.1, R112.2, U9.3 (+IN), U9.5 (+IN), U9.10 (+IN), U9.11 (V-), U9.12 (+IN), U10.3 (+IN), U10.5 (+IN), U10.10 (+IN), U10.11 (V-), U10.12 (+IN), U11.3 (+IN), U11.5 (+IN), U11.10 (+IN), U11.11 (V-), U11.12 (+IN); also elsewhere on the board
J_AUX_NORMAL: R52.2, U8.5 (+IN); also elsewhere on the board
J_DENSITY_CV: R14.1; also elsewhere on the board
J_FEEDBACK_CV: R21.1; also elsewhere on the board
J_GATE_HOLD: R54.1; also elsewhere on the board
J_GATE_TRIG: R56.1; also elsewhere on the board
J_MIX_CV: R32.1; also elsewhere on the board
J_PAN_CV: R26.1; also elsewhere on the board
J_PITCH_CV: R9.1; also elsewhere on the board
J_POSITION_CV: R20.1; also elsewhere on the board
J_SIZE_CV: R3.1; also elsewhere on the board
J_TEXT_CV: R44.1; also elsewhere on the board
J_VERB_CV: R39.1; also elsewhere on the board
J_VOCT_CV: R49.1; also elsewhere on the board
MIX_CV: C23.2, R35.2, U10.14 (OUT); also elsewhere on the board
unnamed: C15.1, R3.2, R6.1, R40.2, U9.6 (-IN)
unnamed: C16.1, R9.2, R11.1, R38.2, U9.9 (-IN)
unnamed: C17.1, R14.2, R16.1, R36.2, U9.13 (-IN)
unnamed: C20.1, R21.2, R23.1, R43.2, U10.6 (-IN)
unnamed: C21.1, R26.2, R28.1, R42.2, U10.9 (-IN)
unnamed: C23.1, R31.2, R32.2, R35.1, U10.13 (-IN)
unnamed: C24.1, R33.2, R39.2, R41.1, U11.2 (-IN)
unnamed: C25.1, R34.2, R44.2, R46.1, U10.2 (-IN)
unnamed: R53.2, U8.6 (-IN), U8.7 (OUT)
unnamed: Q1.B, R54.2
unnamed: C26.1, R49.2, R50.2, R51.1, U11.6 (-IN)
unnamed: Q2.B, R56.2
unnamed: C34.1, R20.2, R37.1, R45.2, U9.2 (-IN)
unnamed: U11.8 (OUT), U11.9 (-IN)
unnamed: U11.13 (-IN), U11.14 (OUT)
unnamed: R111.2, R112.1, U8.2 (-IN)
PITCH_CV: C16.2, R11.2, U9.8 (OUT); also elsewhere on the board
POSITION_CV: C34.2, R37.2, U9.1 (OUT); also elsewhere on the board
SHAPE_CV: C25.2, R46.2, U10.1 (OUT); also elsewhere on the board
SIZE_CV: C15.2, R6.2, U9.7 (OUT); also elsewhere on the board
SPACE_CV: C24.2, R41.2, U11.1 (OUT); also elsewhere on the board
VOCT_CV: C26.2, R51.2, U11.7 (OUT); also elsewhere on the board
WIDTH_CV: C21.2, R28.2, U10.8 (OUT); also elsewhere on the board

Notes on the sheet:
VERB_CV
TEXT_CV
PAN_CV
